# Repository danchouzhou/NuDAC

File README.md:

# NuDAC
A USB codec based on Nuvoton M482ZGCAE MCU and NAU88L25YGB I2S audio codec

## Fetures
### Design
- Provide almost all of MCU I/O on pin header  
- Low noise & fail-safe power design  
- Four-layer PCB  
- Low profile mid mount THT phone jack  
- On board APA ELECTRONIC CO., LTD. patented RGB LED with level translator  
- Molex USB 2.0 through hole Type-C connector improve mechanical strength  
- Jump free Nu-Link connectivity
- Support semi-auto USB ISP (by pressing reset button) provide firmware update and secondary development without a programmer  
### Nuvoton M482ZGCAE microcontroller  
- ARM Cortex-M4 processor up to 192MHz with float point unit and DSP  
- 16-channel programable peripheral direct memory access  
- USB 2.0 full-speed with precise internal oscillator  
- Rich interface include UART, SPI, IIC, IIS, LIN
- 12-bit ADC and DAC
- 16-bit PWM
- True random number generator  
### Nuvoton NAU88L25YGB high performance audio codec
- On chip ground referenced Class-A/AB/G selectable headphone amplifier
- On chip DSP include DRC (Dynamic Range Compressor), and programmable biquad filters  
- 24-bit A/D and D/A signal processing unit, up to 192K sample rate  
- 124dB SNR (@ 1Vrms, 0dB gain, 1KHz)  
- THD+Noise -89dB (@ 32 ohm, 1KHz, 20mW)  
- 28mW output power (@ 32 ohm, 1% THD+N)  

## Specification
- 5V power supply: 4.5~5.5V, 1A max  
- 5V output capacity: 1A max
- VDD output capacity: 300mA max

## To clone this project
This project work with M480BSP submodule from Nuvoton corporation. You need to initialize submodules by passing ``--recurse-submodules`` to the ``git clone`` command.
```
git clone https://github.com/danchouzhou/NuDAC --recurse-submodules
```

## Prepare develop environment
1. Installing tools
```
sudo apt install kicad build-essential gcc-arm-none-eabi libtool libusb-1.0-0-dev
```
2. Build and install customize version of OpenOCD for Nuvoton devices
```
git clone https://github.com/OpenNuvoton/OpenOCD-Nuvoton.git
cd OpenOCD-Nuvoton
./bootstrap
./configure --enable-nulink
make
sudo make install
```

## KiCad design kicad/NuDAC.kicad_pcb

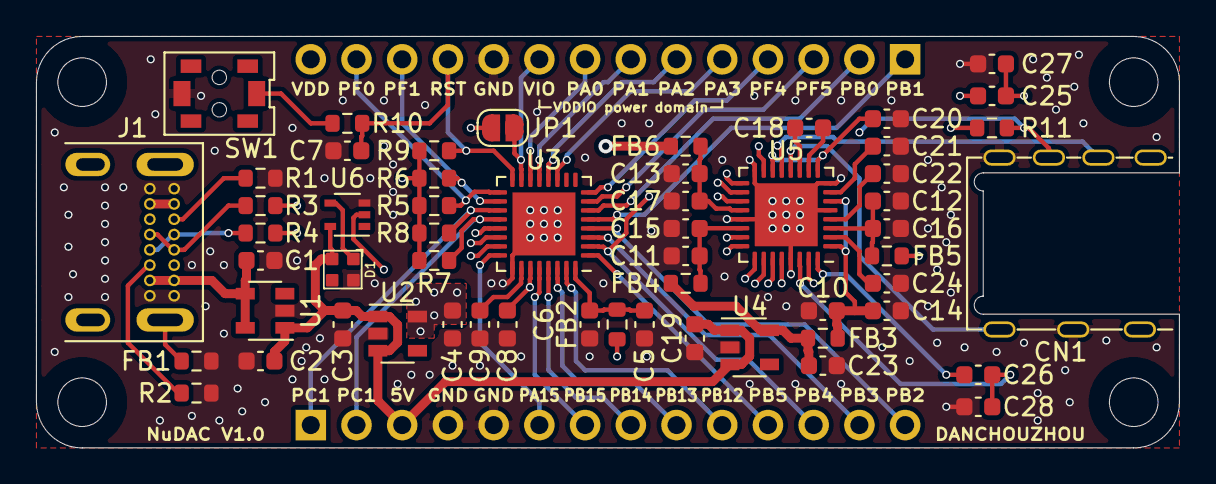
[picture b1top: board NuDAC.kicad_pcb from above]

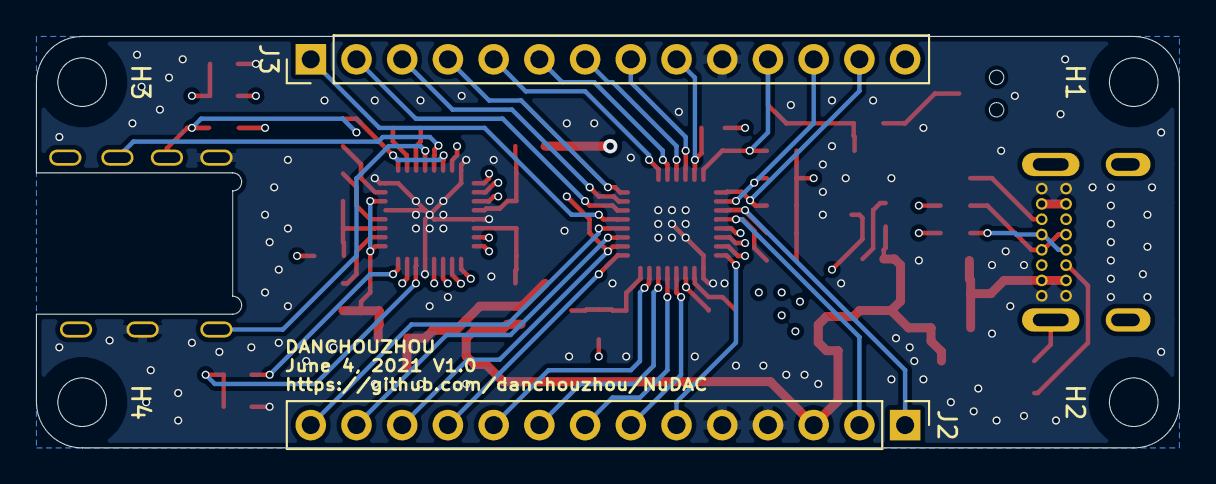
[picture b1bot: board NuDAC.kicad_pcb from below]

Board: 4 copper layers, 63.5 x 22.9 mm, 62 parts (6 on the bottom side), 56 nets.

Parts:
C1, C6, C14, C15, C16, C17: 100nF; C_0603_1608Metric
C2: 100uF; C_0603_1608Metric
C3, C4, C9, C18, C19, C20, C21, C23: 2.2uF; C_0603_1608Metric
C5: 1uF; C_0603_1608Metric
C7, C8: 10uF; C_0603_1608Metric
C10, C11, C12, C13, C22, C24, C25, C26: 4.7uF; C_0603_1608Metric
C27, C28: 1nF; C_0603_1608Metric
CN1: 2SJ3080-000111F
D1: APA-104-2020-5mA
FB1, FB2, FB3, FB4, FB5, FB6: bead; R_0603_1608Metric
H1, H2, H3, H4: MountingHole; MountingHole_2.7mm_M2.5_ISO7380
J1: 2137160001
J2, J3: Conn_01x14; PinHeader_1x14_P2.54mm_Vertical
JP1: SolderJumper_2_Open; SolderJumper-2_P1.3mm_Open_RoundedPad1.0x1.5mm
R1, R2: 5K1; R_0603_1608Metric
R3, R4: 33R; R_0603_1608Metric
R5, R6: 100K; R_0603_1608Metric
R7, R8: 4K7; R_0603_1608Metric
R9: 10K; R_0603_1608Metric
R10: 68R; R_0603_1608Metric
R11: 1M; R_0603_1608Metric
SW1: PTS820
U1: TPS2065CDBVR-2; SOT-23-5
U2: MCP1812BT-033_OT; SOT-23-5
U3: M482ZGCAE; VQFN-32-1EP_5x5mm_P0.5mm_EP3.5x3.5mm
U4: MCP1812AT-018_OT; SOT-23-5
U5: NAU88L25YGB; VQFN-32-1EP_5x5mm_P0.5mm_EP3.5x3.5mm
U6: SN74LV1T34DCK; SOT-353_SC-70-5

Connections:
+1V8: C23.1, FB3.2, FB4.2, U4.5
+3V3: C4.1, C8.1, FB2.2, FB5.2, FB6.2, J3.14, JP1.1, R5.2, R6.2, R7.2, R8.2, R9.2, U2.5, U3.27
+5V: C2.1, C3.1, C19.1, D1.2, J2.3, U1.1, U2.1, U2.3, U4.1, U4.3, U6.5
/Codec/HPL: CN1.1, U5.12
/Codec/HPR: CN1.2, U5.13
/Codec/JKDET: CN1.6, R11.1, U5.27
/Codec/JKR2: C26.1, C28.1, CN1.3, U5.30
/Codec/JKSLV: C25.1, C27.1, CN1.4, U5.28
/Codec/MIC+: C25.2, U5.31
/Codec/MIC-: C26.2, U5.32
/Codec/VDDA: C10.1, C14.1, FB3.1, R11.2, U5.1, U5.6
/Codec/VDDB: C13.1, C17.1, FB6.1, U5.20
/Codec/VDDC: C11.1, C15.1, FB4.1, U5.22
/Codec/VDDMIC: C12.1, C16.1, FB5.1, U5.3
/MCU/AVDD: C5.1, C6.1, FB2.1, U3.32
GND: C1.2, C2.2, C3.2, C4.2, C5.2, C6.2, C7.2, C8.2, C9.2, C10.2, C11.2, C12.2, C13.2, C14.2, C15.2, C16.2, C17.2, C19.2, C20.2, C21.2, C22.2, C23.2, C24.2, C27.2, C28.2, CN1.5, CN1.MS, D1.4, FB1.1, J1.A1, J1.A12, J1.B1, J1.B12, J2.4, J2.5, J3.10, R1.1, R2.1, SW1.2, U1.2, U2.2, U3.25, U3.33, U4.2, U5.5, U5.8, U5.16, U5.21, U5.29, U5.33, U6.3
I2C0_SCL: J2.1, R8.1, U3.19, U5.18
I2C0_SDA: J2.2, R7.1, U3.20, U5.17
I2S_BCLK: J2.11, U3.1, U5.26
I2S_DI: J2.13, U3.3, U5.24
I2S_DO: J2.14, U3.4, U5.25
I2S_LRCK: J3.1, U3.5, U5.23
I2S_MCLK: J2.12, U3.2, U5.19
ICE_CLK: J3.12, R6.1, U3.18
ICE_DAT: J3.13, R5.1, U3.17
unnamed: C9.1, U3.26
unnamed: C18.1, U5.10
unnamed: C18.2, U5.11
unnamed: C20.1, U5.9, U5.14
unnamed: C21.1, U5.7
unnamed: C22.1, U5.4
unnamed: C24.1, U5.2
unnamed: D1.1, U6.4
unnamed: FB1.2, J1.S1
unnamed: J1.A5, R1.2
unnamed: J1.A6, J1.B6, R4.2
unnamed: J1.A7, J1.B7, R3.2
unnamed: J1.B5, R2.2
unnamed: R10.2, SW1.1
PA0: J3.8, U3.14
PA1: J3.7, U3.13
PA2: J3.6, U3.12
PA3: J3.5, U3.11
PA15: J2.6, U3.24, U6.2
PB0: J3.2, U3.6, U5.15
PB12: J2.10, U3.31
PB13: J2.9, U3.30
PB14: J2.8, U3.29
PB15: J2.7, U3.28
PF4: J3.4, U3.8
PF5: J3.3, U3.7
USB_DN: R3.1, U3.22
USB_DP: R4.1, U3.23
VBUS: C1.1, J1.A4, J1.A9, J1.B4, J1.B9, U1.4, U1.5, U3.21
VDDIO: J3.9, JP1.2, U3.15
nRESET: C7.1, J3.11, R9.1, R10.1, U3.16

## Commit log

2021-08-15 Upload KiCad files
2021-08-15 reorganize directory, add PCB image
2021-08-15 Adjust the order of schematic
2021-08-16 Update schematic PDF
2021-08-16 Add submodule
2021-08-23 Add ISP firmware
2021-08-23 Remove Objects
2021-09-11 Change detect pin into PA15
2021-09-11 Fix SysTick->LOAD overflow issue
2021-09-11 Add ISP_HID_AUTO
2021-09-11 Provide ISP_HID auto detect function
2021-09-25 Add NeoPixel
2021-09-25 Support for M480BSP
2021-10-06 Add replacement part number for level shifter
2022-01-01 Change pin mode resolving method
2022-01-02 Fix HIRC stability issue
2022-01-02 Fix HIRC stability and SysTick overflow issue
2022-01-02 Add return value avoid from warnimg
2022-01-02 Remove NeoPixel
2022-01-02 Add silkscreen comment
2022-01-03 Remove delay
2022-01-09 Add NeoPixel status indicator
2022-01-10 Update SYS_Init()
2022-01-10 Add SineWave
2022-01-16 Add main function
2022-01-16 Add CMSIS DSP_Lib
2022-01-16 Fix carriage return mistake
2022-01-16 Update Makefile
2022-01-17 Rename the project
2022-01-27 Remove DSP_Lib_Test
2022-01-27 Rename folder
2022-01-27 Add signal function generator
2022-01-27 Update print message
2022-02-08 Add NAU88L25 codec library
2022-02-08 Add 1KHz sine wave generator
2022-07-29 Fix the max value issue of delayMicroseconds
2022-07-29 Add timeout function
2022-08-08 Update Makefile
    1. Separate BSP, library and user code to decrease compile time
2022-08-09 Remove old files
2022-08-09 Update linker script
2022-10-02 Update to KiCad 6
